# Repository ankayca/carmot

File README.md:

# Carmot
This is an open source esp32s2 board project.
Carmot: The substance believed to be the main ingredient of the Philosopher's Stone.

# Aim
Design a board which will be a miles stone of IOT projects. This board will be IOT 's arduino. So who want to learn IOT apps with proffesional techniques (like use led strip, motor, relay ).

# Note for collaborators :

I am an elecktrical electronic engineer and I work on this to create a different perspective of IOT. I need help to designing board and programming (I am using esp-idf). If you agree to work together , I guarantee that we will change this IOT ecosystem together.

If you have the experience or motivation to will be expert of this zones:
            (pcb design,
            internet protocols(TCP-IP , websocket,udp , etc.),
            esp-idf ,
            circuit design)
            I will feel honor to work with you.
# Contact: 
  email :ankayca2121@gmail.com

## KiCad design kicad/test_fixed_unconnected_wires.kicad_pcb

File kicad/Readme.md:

# Notes:
26_02_21.kicad_pcb : revision 2.1
test_fixed_unconnected_wires.kicad_pcb : revision 1.0

test_fixed_unconnected_wires.kicad_pcb work perfectly.

# Important
At 26_02_21.kicad_pcb we try to design more cheapest board to everyone can easily generate and start to be a philosopher of Carmot. 

### Regards from carmot !!!!

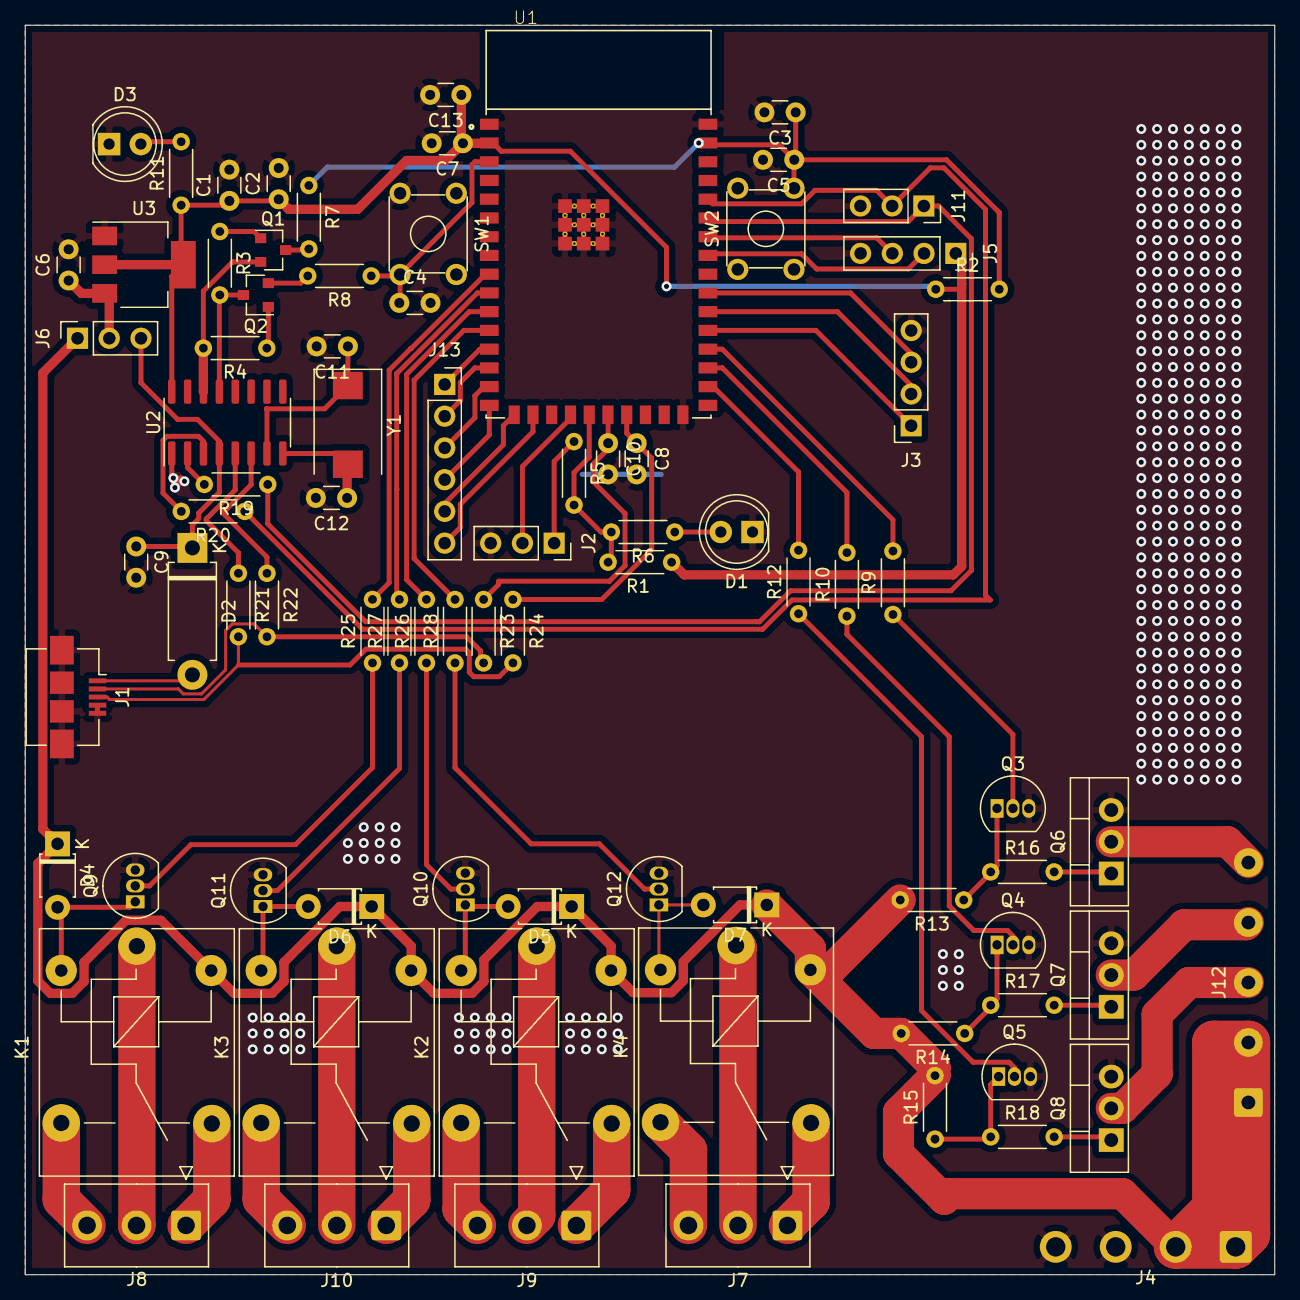
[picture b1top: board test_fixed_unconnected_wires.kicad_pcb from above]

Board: 2 copper layers, 100.0 x 100.0 mm, 83 parts (0 on the bottom side), 81 nets.

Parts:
C1: 10uF/25V; C_Disc_D3.0mm_W1.6mm_P2.50mm
C2: 0.1uF/16V; C_Disc_D3.0mm_W1.6mm_P2.50mm
C3: 1uf/10V; C_Disc_D3.0mm_W1.6mm_P2.50mm
C4, C5: 0.1uF; C_Disc_D3.0mm_W1.6mm_P2.50mm
C6, C13: 100nF; C_Disc_D3.0mm_W1.6mm_P2.50mm
C7: 22uF; C_Disc_D3.0mm_W1.6mm_P2.50mm
C8, C10, C11, C12: 22pF; C_Disc_D3.0mm_W1.6mm_P2.50mm
C9: 10uF; C_Disc_D3.0mm_W1.6mm_P2.50mm
D1: LED_GREEN; LED_D5.0mm
D2: 1N5819; D_DO-15_P10.16mm_Horizontal
D3: RED_LED; LED_D5.0mm
D4, D5, D6, D7: 1N4148; D_T-1_P5.08mm_Horizontal
J1: USB_B_Micro; USB_Micro-B_Amphenol_10104110_Horizontal
J2, J11: Conn_01x03_Female; PinSocket_1x03_P2.54mm_Vertical
J3: Conn_01x04_Male; PinSocket_1x04_P2.54mm_Vertical
J4: Conn_01x04_Female; SolderWire-0.75sqmm_1x04_P4.8mm_D1.25mm_OD2.3mm
J5: Conn_01x04_Female; PinSocket_1x04_P2.54mm_Vertical
J6: Conn_01x03_Male; PinSocket_1x03_P2.54mm_Vertical
J7, J8, J9, J10: Conn_01x03_Female; TE_826576-3_1x03_P3.96mm_Vertical
J12: Conn_01x05_Female; SolderWire-0.5sqmm_1x05_P4.8mm_D0.9mm_OD2.3mm
J13: Conn_01x06_Male; PinSocket_1x06_P2.54mm_Vertical
K1, K2, K3, K4: SANYOU_SRD_Form_C; Relay_SPDT_SANYOU_SRD_Series_Form_C
Q1, Q2: BC817; SOT-23
Q3, Q4, Q5, Q9, Q10, Q11, Q12: BC547; TO-92_Inline
Q6, Q7, Q8: IRLZ44N; TO-220-3_Vertical
R1, R2, R3, R4: 10K; R_Axial_DIN0204_L3.6mm_D1.6mm_P5.08mm_Horizontal
R5, R6, R19, R20, R21, R22, R23, R24: 0; R_Axial_DIN0204_L3.6mm_D1.6mm_P5.08mm_Horizontal
R7, R8: 0R; R_Axial_DIN0204_L3.6mm_D1.6mm_P5.08mm_Horizontal
R9, R10, R12: 5K; R_Axial_DIN0204_L3.6mm_D1.6mm_P5.08mm_Horizontal
R11: 5.1K; R_Axial_DIN0204_L3.6mm_D1.6mm_P5.08mm_Horizontal
R13, R14, R15, R25, R26, R27, R28: 1K; R_Axial_DIN0204_L3.6mm_D1.6mm_P5.08mm_Horizontal
R16, R17, R18: 200R; R_Axial_DIN0204_L3.6mm_D1.6mm_P5.08mm_Horizontal
SW1, SW2: SW_Push_Open_Dual; SW_TH_Tactile_Omron_B3F-10xx
U1: ESP32-S2-WROOM; XCVR_ESP32-S2-WROOM
U2: CH340G; SOIC-16_3.9x9.9mm_P1.27mm
U3: AMS1117-3.3; SOT-223-3_TabPin2
Y1: 12Mhz; Crystal_SMD_FOX_FE-2Pin_7.5x5.0mm

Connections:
+3V3: C1.1, C2.1, C7.1, C13.1, J5.1, R1.2, R2.1, R11.1, U1.2, U2.16, U3.2
+5V: C9.1, D2.1, J6.3, U2.4
+12V: D4.1, D5.1, D6.1, D7.1, J4.1, J4.2, J6.1, J12.1, J12.2, K1.5, K2.5, K3.5, K4.5, R13.2, R14.2, R15.2
CHIP_PU: C3.1, C5.1, R2.2, R7.1, SW2.4, U1.41
DTR: Q2.3, R3.2, U2.13
EN_Auto: Q1.3, R7.2
GND: C1.2, C2.2, C3.2, C4.2, C5.2, C6.2, C7.2, C8.2, C9.2, C10.2, C11.2, C12.2, C13.2, D1.1, D3.1, J1.4, J1.5, J1.6, J2.3, J3.4, J4.3, J4.4, J5.4, J11.3, Q3.3, Q4.3, Q5.3, Q6.3, Q7.3, Q8.3, Q9.3, Q10.3, Q11.3, Q12.3, SW1.3, SW2.3, U1.1, U1.26, U1.42, U1.43.1, U1.43.2, U1.43.3, U1.43.4, U1.43.5, U1.43.6, U1.43.7, U1.43.8, U1.43.9, U1.43.10, U1.43.11, U1.43.12, U1.43.13, U1.43.14, U1.43.15, U1.43.16, U1.43.17, U1.43.18, U1.43.19, U1.43.20, U1.43.21, U2.1, U3.1
GPIO0: C4.1, R8.1, SW1.4, U1.3
GPIO6: R25.2, U1.9
GPIO7: R27.2, U1.10
GPIO8: R26.2, U1.11
GPIO9: R28.2, U1.12
GPIO10: J13.1, U1.13
GPIO11: J13.2, U1.14
GPIO12: J13.3, U1.15
GPIO13: J13.4, U1.16
GPIO14: J13.5, U1.17
GPIO15: J13.6, U1.18
GPIO18: R1.1, R5.2, R6.2, U1.21
GPIO19: C10.1, R23.1, U1.22
GPIO20: C8.1, R24.1, U1.23
GPIO34: R12.2, U1.28
GPIO35: R10.2, U1.29
GPIO36: R9.2, U1.30
GPIO37: J3.1, U1.31
GPIO38: J3.2, U1.32
GPIO39: J3.3, U1.33
IO0_Auto: Q2.2, R8.2
LED_B: J12.5, Q6.2
LED_G: J12.3, Q8.2
LED_R: J12.4, Q7.2
unnamed: C11.1, U2.7, Y1.1
unnamed: C12.1, U2.8, Y1.2
unnamed: D1.2, R6.1
unnamed: D2.2, J1.1
unnamed: D3.2, R11.2
unnamed: D4.2, K1.2, Q9.1
unnamed: D5.2, K2.2, Q10.1
unnamed: D6.2, K3.2, Q11.1
unnamed: D7.2, K4.2, Q12.1
unnamed: J1.2, R22.2, R23.2
unnamed: J1.3, R21.2, R24.2
unnamed: Q1.1, R3.1
unnamed: Q2.1, R4.1
unnamed: Q3.1, R13.1, R16.1
unnamed: Q3.2, R9.1
unnamed: Q4.1, R14.1, R17.1
unnamed: Q4.2, R10.1
unnamed: Q5.1, R15.1, R18.1
unnamed: Q5.2, R12.1
unnamed: Q6.1, R16.2
unnamed: Q7.1, R17.2
unnamed: Q8.1, R18.2
unnamed: Q9.2, R25.1
unnamed: Q10.2, R26.1
unnamed: Q11.2, R27.1
unnamed: Q12.2, R28.1
unnamed: R19.2, U2.2
unnamed: R20.2, U2.3
RTS: Q1.2, R4.2, U2.14
RXD0: J11.2, R20.1, U1.38
RXD1: J2.1, R5.1
Rly1_1: J10.2, K3.1
Rly1_2: J10.1, K3.4
Rly1_3: J10.3, K3.3
Rly2_1: J9.2, K2.1
Rly2_2: J9.1, K2.4
Rly2_3: J9.3, K2.3
Rly3_1: J8.2, K1.1
Rly3_2: J8.1, K1.4
Rly3_3: J8.3, K1.3
Rly4_1: J7.2, K4.1
Rly4_2: J7.1, K4.4
Rly4_3: J7.3, K4.3
SCL: J5.3, U1.36
SDA: J5.2, U1.35
TXD0: J11.1, R19.1, U1.37
TXD1: J2.2, U1.20
USB_DN: R22.1, U2.6
USB_DP: R21.1, U2.5
VCC: C6.1, J6.2, U3.3

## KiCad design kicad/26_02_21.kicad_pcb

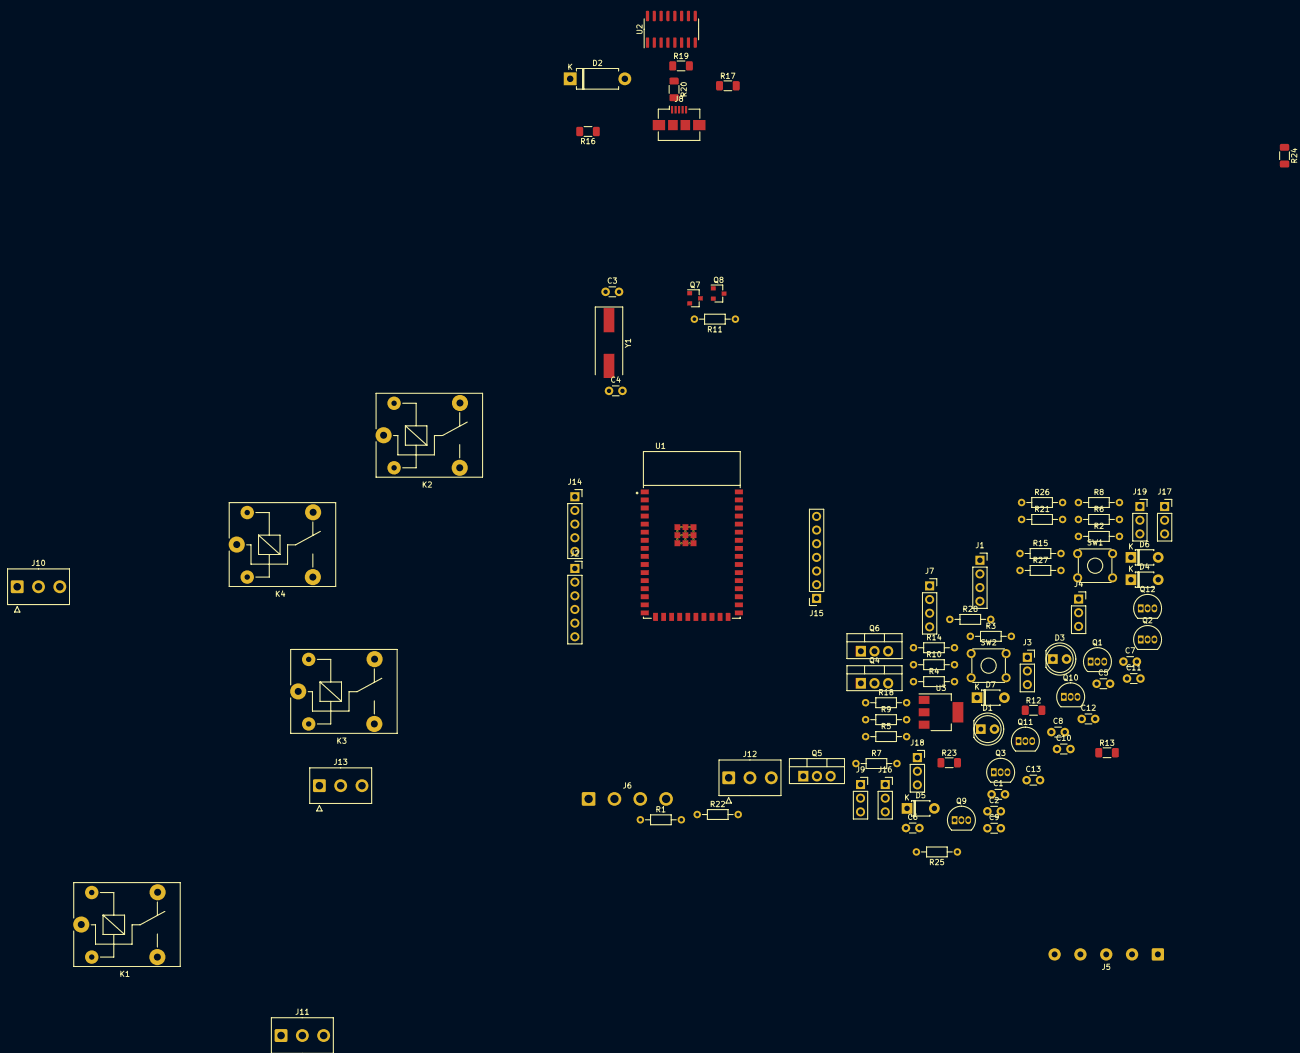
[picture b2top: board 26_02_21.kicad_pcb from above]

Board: 2 copper layers, 89 parts (0 on the bottom side), 93 nets, no tracks yet.

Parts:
C1: 22uF; C_Disc_D3.0mm_W1.6mm_P2.50mm
C2, C5, C6: 0.1uF; C_Disc_D3.0mm_W1.6mm_P2.50mm
C3, C4, C12, C13: 22pF; C_Disc_D3.0mm_W1.6mm_P2.50mm
C7, C9: 10uf; C_Disc_D3.0mm_W1.6mm_P2.50mm
C8: 1uf/10V; C_Disc_D3.0mm_W1.6mm_P2.50mm
C10: 10uF; C_Disc_D3.0mm_W1.6mm_P2.50mm
C11: 100nF; C_Disc_D3.0mm_W1.6mm_P2.50mm
D1: LED_GREEN; LED_D5.0mm
D2: 1N5819; D_DO-15_P10.16mm_Horizontal
D3: RED_LED; LED_D5.0mm
D4, D5, D6, D7: 1N4148; D_T-1_P5.08mm_Horizontal
J1: Conn_01x04_Male; PinSocket_1x04_P2.54mm_Vertical
J2: Conn_01x06_Male; PinSocket_1x06_P2.54mm_Vertical
J3, J4: Conn_01x03_Female; PinSocket_1x03_P2.54mm_Vertical
J5: Conn_01x05_Female; SolderWire-0.5sqmm_1x05_P4.8mm_D0.9mm_OD2.3mm
J6: Conn_01x04_Female; SolderWire-0.75sqmm_1x04_P4.8mm_D1.25mm_OD2.3mm
J7: Conn_01x04_Female; PinSocket_1x04_P2.54mm_Vertical
J8: USB_B_Micro; USB_Micro-B_Amphenol_10104110_Horizontal
J9, J16, J17, J18, J19: Conn_01x03_Male; PinSocket_1x03_P2.54mm_Vertical
J10, J11, J12, J13: Conn_01x03_Female; TE_826576-3_1x03_P3.96mm_Vertical
J14: Conn_01x05_Male; PinSocket_1x05_P2.54mm_Vertical
J15: Conn_01x07_Male; PinSocket_1x07_P2.54mm_Vertical
K1, K2, K3, K4: SANYOU_SRD_Form_C; Relay_SPDT_SANYOU_SRD_Series_Form_C
Q1, Q2, Q3, Q9, Q10, Q11, Q12: BC547; TO-92_Inline
Q4, Q5, Q6: IRLZ44N; TO-220-3_Vertical
Q7, Q8: BC817; SOT-23
R1, R2, R3: 5K; R_Axial_DIN0204_L3.6mm_D1.6mm_P7.62mm_Horizontal
R4, R5, R6, R25, R26, R27, R28: 1K; R_Axial_DIN0204_L3.6mm_D1.6mm_P7.62mm_Horizontal
R7, R8, R9: 200R; R_Axial_DIN0204_L3.6mm_D1.6mm_P7.62mm_Horizontal
R10, R11, R18, R21: 10K; R_Axial_DIN0204_L3.6mm_D1.6mm_P7.62mm_Horizontal
R12, R13, R16, R17, R19, R20, R23, R24: 0; R_1206_3216Metric_Pad1.30x1.75mm_HandSolder
R14, R15: 0R; R_Axial_DIN0204_L3.6mm_D1.6mm_P7.62mm_Horizontal
R22: 5.1K; R_Axial_DIN0204_L3.6mm_D1.6mm_P7.62mm_Horizontal
SW1, SW2: SW_Push_Open_Dual; SW_TH_Tactile_Omron_B3F-10xx
U1: ESP32-S2-WROOM; XCVR_ESP32-S2-WROOM
U2: CH340G; SOIC-16_3.9x9.9mm_P1.27mm
U3: AMS1117-3.3; SOT-223-3_TabPin2
Y1: 12Mhz; Crystal_SMD_HC49-SD

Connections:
+3V3: C1.1, C2.1, C9.1, C11.1, J7.1, J17.1, J17.2, J17.3, R18.2, R21.1, R22.1, U1.2, U2.4, U2.16, U3.2
+5V: C10.1, D2.1, D4.1, D5.1, D6.1, D7.1, J9.3, J16.1, J16.2, J16.3, K1.5, K2.5, K3.5, K4.5
+12V: J5.1, J5.2, J6.1, J6.2, J9.1, J18.1, J18.2, J18.3, R4.2, R5.2, R6.2
CHIP_PU: C6.1, C8.1, R14.1, R21.2, SW2.1, SW2.2, U1.41
DTR: Q8.3, R10.2, U2.13
EN_Auto: Q7.3, R14.2
GND: C1.2, C2.2, C3.2, C4.2, C5.2, C6.2, C7.2, C8.2, C9.2, C10.2, C11.2, C12.2, C13.2, D1.1, D3.1, J3.3, J4.3, J6.3, J6.4, J7.4, J8.4, J8.5, J8.6, J19.1, J19.2, J19.3, Q1.3, Q2.3, Q3.3, Q4.3, Q5.3, Q6.3, Q9.3, Q10.3, Q11.3, Q12.3, SW1.3, SW1.4, SW2.3, SW2.4, U1.1, U1.26, U1.42, U1.43.1, U1.43.2, U1.43.3, U1.43.4, U1.43.5, U1.43.6, U1.43.7, U1.43.8, U1.43.9, U1.43.10, U1.43.11, U1.43.12, U1.43.13, U1.43.14, U1.43.15, U1.43.16, U1.43.17, U1.43.18, U1.43.19, U1.43.20, U1.43.21, U2.1, U3.1
GPIO0: C5.1, R15.1, SW1.1, SW1.2, U1.3
GPIO1: J14.1, U1.4
GPIO2: J14.2, U1.5
GPIO3: J14.3, U1.6
GPIO4: J14.4, U1.7
GPIO5: J14.5, U1.8
GPIO6: R25.2, U1.9
GPIO7: R27.2, U1.10
GPIO8: R26.2, U1.11
GPIO9: R28.2, U1.12
GPIO10: J2.1, U1.13
GPIO11: J2.2, U1.14
GPIO12: J2.3, U1.15
GPIO13: J2.4, U1.16
GPIO14: J2.5, U1.17
GPIO15: J2.6, U1.18
GPIO16: J15.1, U1.19
GPIO18: R12.2, R13.2, R18.1, U1.21
GPIO19: C12.1, R23.1, U1.22
GPIO20: C13.1, R24.1, U1.23
GPIO21: J15.2, U1.24
GPIO26: J15.3, U1.25
GPIO33: J15.4, U1.27
GPIO34: R3.2, U1.28
GPIO35: R2.2, U1.29
GPIO36: R1.2, U1.30
GPIO37: J1.1, U1.31
GPIO38: J1.2, U1.32
GPIO39: J1.3, U1.33
GPIO40: J1.4, J15.5, U1.34
GPIO45: J15.6, U1.39
GPIO46: J15.7, U1.40
IO0_Auto: Q8.2, R15.2
LED_B: J5.5, Q4.2
LED_G: J5.3, Q6.2
LED_R: J5.4, Q5.2
unnamed: C3.1, U2.7, Y1.1
unnamed: C4.1, U2.8, Y1.2
unnamed: D1.2, R13.1
unnamed: D2.2, J8.1
unnamed: D3.2, R22.2
unnamed: D4.2, K1.2, Q9.1
unnamed: D5.2, K2.2, Q10.1
unnamed: D6.2, K3.2, Q11.1
unnamed: D7.2, K4.2, Q12.1
unnamed: J8.2, R20.2, R23.2
unnamed: J8.3, R19.2, R24.2
unnamed: Q1.1, R4.1, R7.1
unnamed: Q1.2, R1.1
unnamed: Q2.1, R5.1, R8.1
unnamed: Q2.2, R2.1
unnamed: Q3.1, R6.1, R9.1
unnamed: Q3.2, R3.1
unnamed: Q4.1, R7.2
unnamed: Q5.1, R8.2
unnamed: Q6.1, R9.2
unnamed: Q7.1, R10.1
unnamed: Q8.1, R11.1
unnamed: Q9.2, R25.1
unnamed: Q10.2, R26.1
unnamed: Q11.2, R27.1
unnamed: Q12.2, R28.1
unnamed: R16.2, U2.2
unnamed: R17.2, U2.3
RTS: Q7.2, R11.2, U2.14
RXD0: J4.2, R16.1, U1.38
RXD1: J3.1, R12.1
Rly1_1: J13.2, K3.1
Rly1_2: J13.1, K3.4
Rly1_3: J13.3, K3.3
Rly2_1: J12.2, K2.1
Rly2_2: J12.1, K2.4
Rly2_3: J12.3, K2.3
Rly3_1: J11.2, K1.1
Rly3_2: J11.1, K1.4
Rly3_3: J11.3, K1.3
Rly4_1: J10.2, K4.1
Rly4_2: J10.1, K4.4
Rly4_3: J10.3, K4.3
SCL: J7.3, U1.36
SDA: J7.2, U1.35
TXD0: J4.1, R17.1, U1.37
TXD1: J3.2, U1.20
USB_DN: R20.1, U2.6
USB_DP: R19.1, U2.5
VCC: C7.1, J9.2, U3.3
